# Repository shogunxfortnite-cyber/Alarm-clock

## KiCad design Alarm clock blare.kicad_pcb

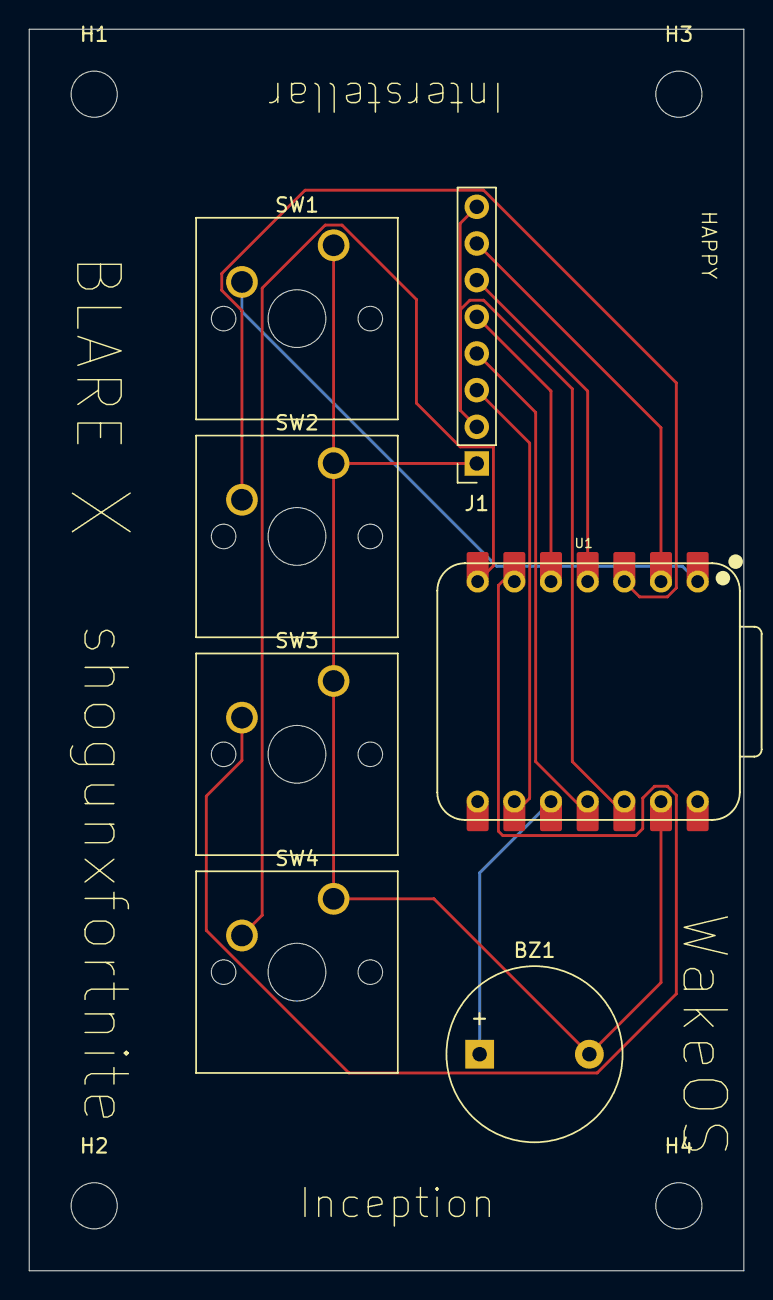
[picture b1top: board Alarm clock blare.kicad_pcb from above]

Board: 2 copper layers, 49.5 x 86.0 mm, 11 parts (0 on the bottom side), 12 nets.

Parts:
BZ1: Buzzer; Buzzer_12x9.5RM7.6
H1, H2, H3, H4: MountingHole; MountingHole_3.2mm_M3
J1: Conn_01x08_Pin; PinSocket_1x08_P2.54mm_Vertical
SW1, SW2, SW3, SW4: SW_Push; SW_Cherry_MX_1.00u_PCB
U1: XIAO-ESP32-C3-SMD; XIAO-ESP32-C3-DIP

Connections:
/+3.3V: J1.2, J1.8, U1.12 (3V3_OUT)
/B1: SW1.2, U1.1 (D0)
/B2: SW2.2, U1.3 (D2)
/B3: SW3.2, U1.6 (D5)
/B4: SW4.2, U1.7 (D6)
/BZ: BZ1.1 (+), U1.10 (D9/BOOT)
/CS: J1.7, U1.2 (D1)
/DC: J1.6, U1.4 (D3)
/GND: BZ1.2 (-), J1.1, SW1.1, SW2.1, SW3.1, SW4.1, U1.13 (GND)
/RST: J1.5, U1.5 (D4)
/SCL: J1.3, U1.9 (D8)
/SDA: J1.4, U1.11 (D10)
